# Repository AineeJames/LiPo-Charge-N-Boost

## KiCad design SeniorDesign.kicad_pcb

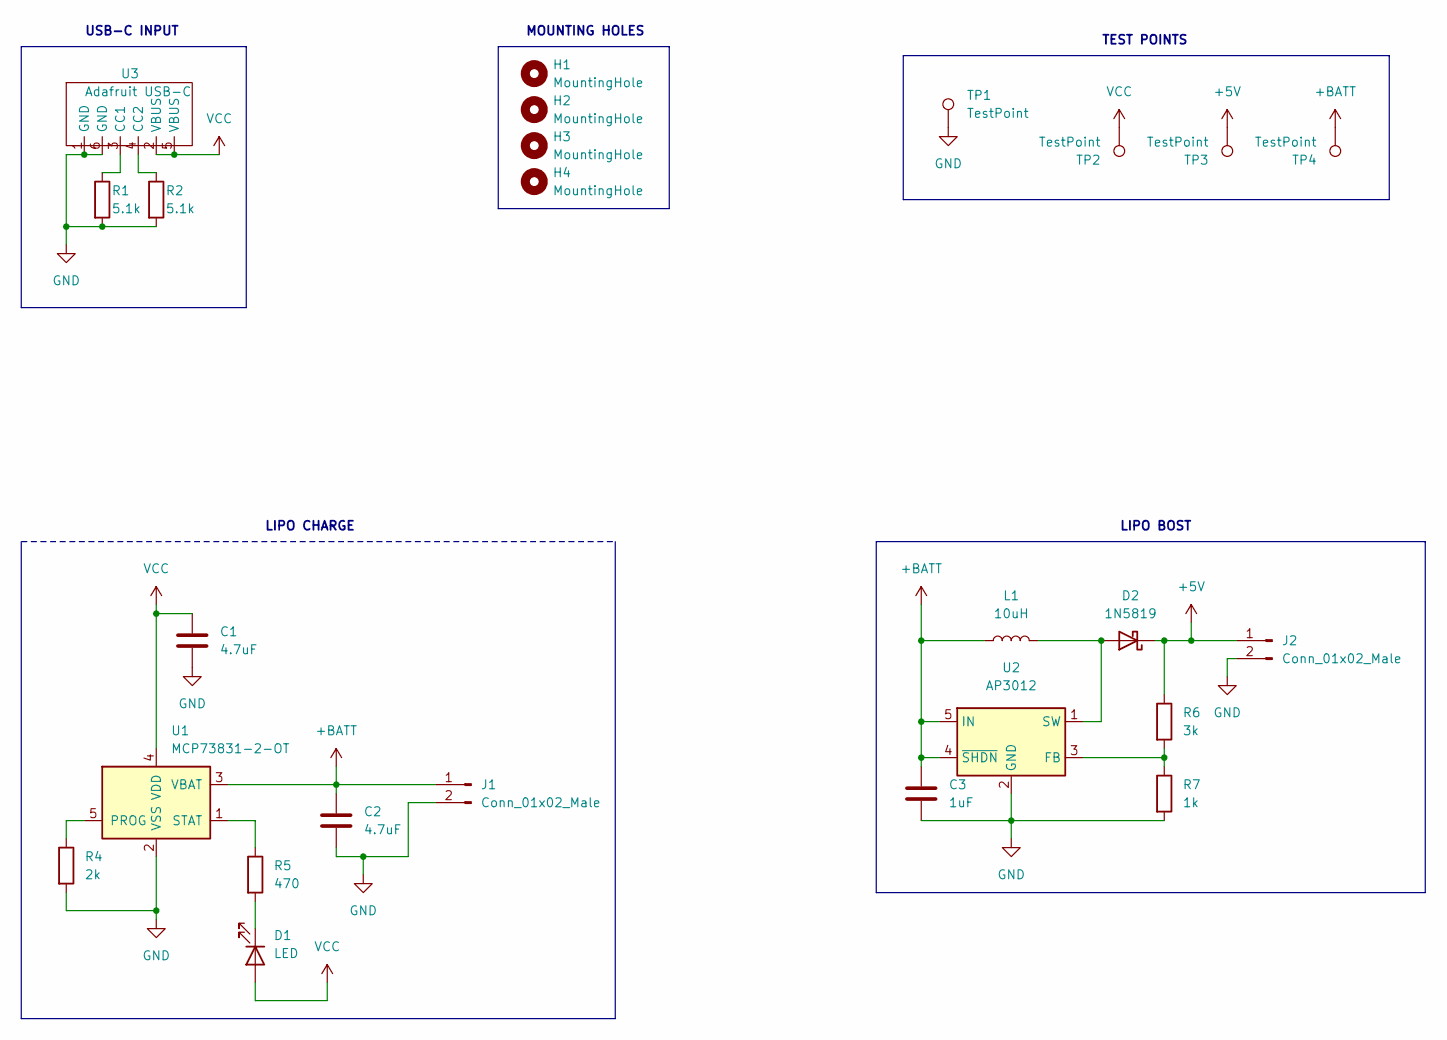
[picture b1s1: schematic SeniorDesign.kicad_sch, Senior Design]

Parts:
C1, C2: 4.7uF; C_0805_2012Metric
C3: 1uF; C_0805_2012Metric
D1: LED; LED_0805_2012Metric
D2: 1N5819; D_SOD-123F
H1, H2, H3, H4: MountingHole; MountingHole_3.2mm_M3_ISO14580_Pad_TopOnly
J1, J2: Conn_01x02_Male; JST_PH_S2B-PH-K_1x02_P2.00mm_Horizontal
L1: 10uH; L_0805_2012Metric
R1, R2: 5.1k; R_0805_2012Metric
R4: 2k; R_0805_2012Metric
R5: 470; R_0805_2012Metric
R6: 3k; R_0805_2012Metric
R7: 1k; R_0805_2012Metric
TP1, TP2, TP3, TP4: TestPoint; TestPoint_Pad_D1.5mm
U1: MCP73831-2-OT; SOT-23-5
U2: AP3012; SOT-23-5
U3: Adafruit USB-C; Adafruit SMD Power Only

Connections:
+5V: D2.1 (K), J2.1, R6.1, TP3.1
+BATT: C2.1, C3.1, J1.1, L1.1, TP4.1, U1.3 (VBAT), U2.4 (~SHDN), U2.5 (IN)
GND: C1.2, C2.2, C3.2, J1.2, J2.2, R1.2, R2.2, R4.2, R7.2, TP1.1, U1.2 (VSS), U2.2 (GND), U3.1 (GND), U3.6 (GND)
unnamed: D1.1 (K), R5.2
unnamed: D2.2 (A), L1.2, U2.1 (SW)
unnamed: R1.1, U3.3 (CC1)
unnamed: R2.1, U3.4 (CC2)
unnamed: R4.1, U1.5 (PROG)
unnamed: R5.1, U1.1 (STAT)
unnamed: R6.2, R7.1, U2.3 (FB)
VCC: C1.1, D1.2 (A), TP2.1, U1.4 (VDD), U3.2 (VBUS), U3.5 (VBUS)

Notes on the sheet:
TEST POINTS
MOUNTING HOLES
LIPO BOST
LIPO CHARGE
USB-C INPUT

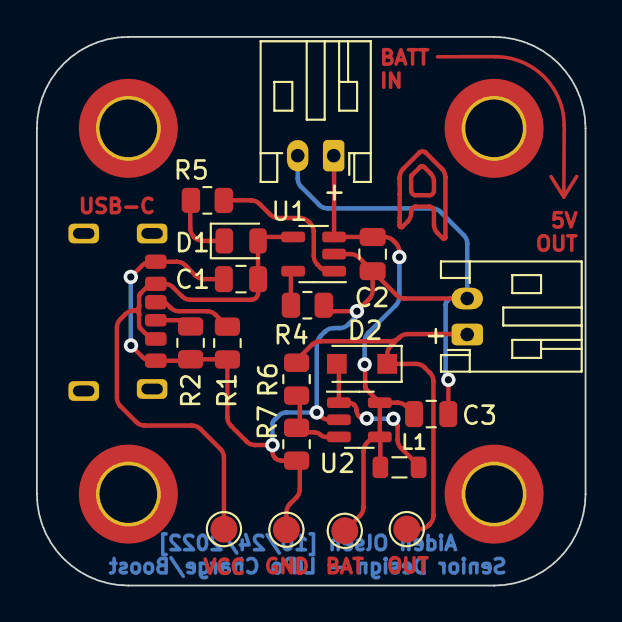
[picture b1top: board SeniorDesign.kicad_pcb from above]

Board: 2 copper layers, 30.5 x 30.5 mm, 25 parts (0 on the bottom side), 11 nets.

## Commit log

2022-11-01 fixed main
